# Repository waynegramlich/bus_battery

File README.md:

# bus_battery
A Bus module that senses battery voltage

## Revision A Issues

* R7 as 220 Ohm 3 resist SIP6 probably should be changed.

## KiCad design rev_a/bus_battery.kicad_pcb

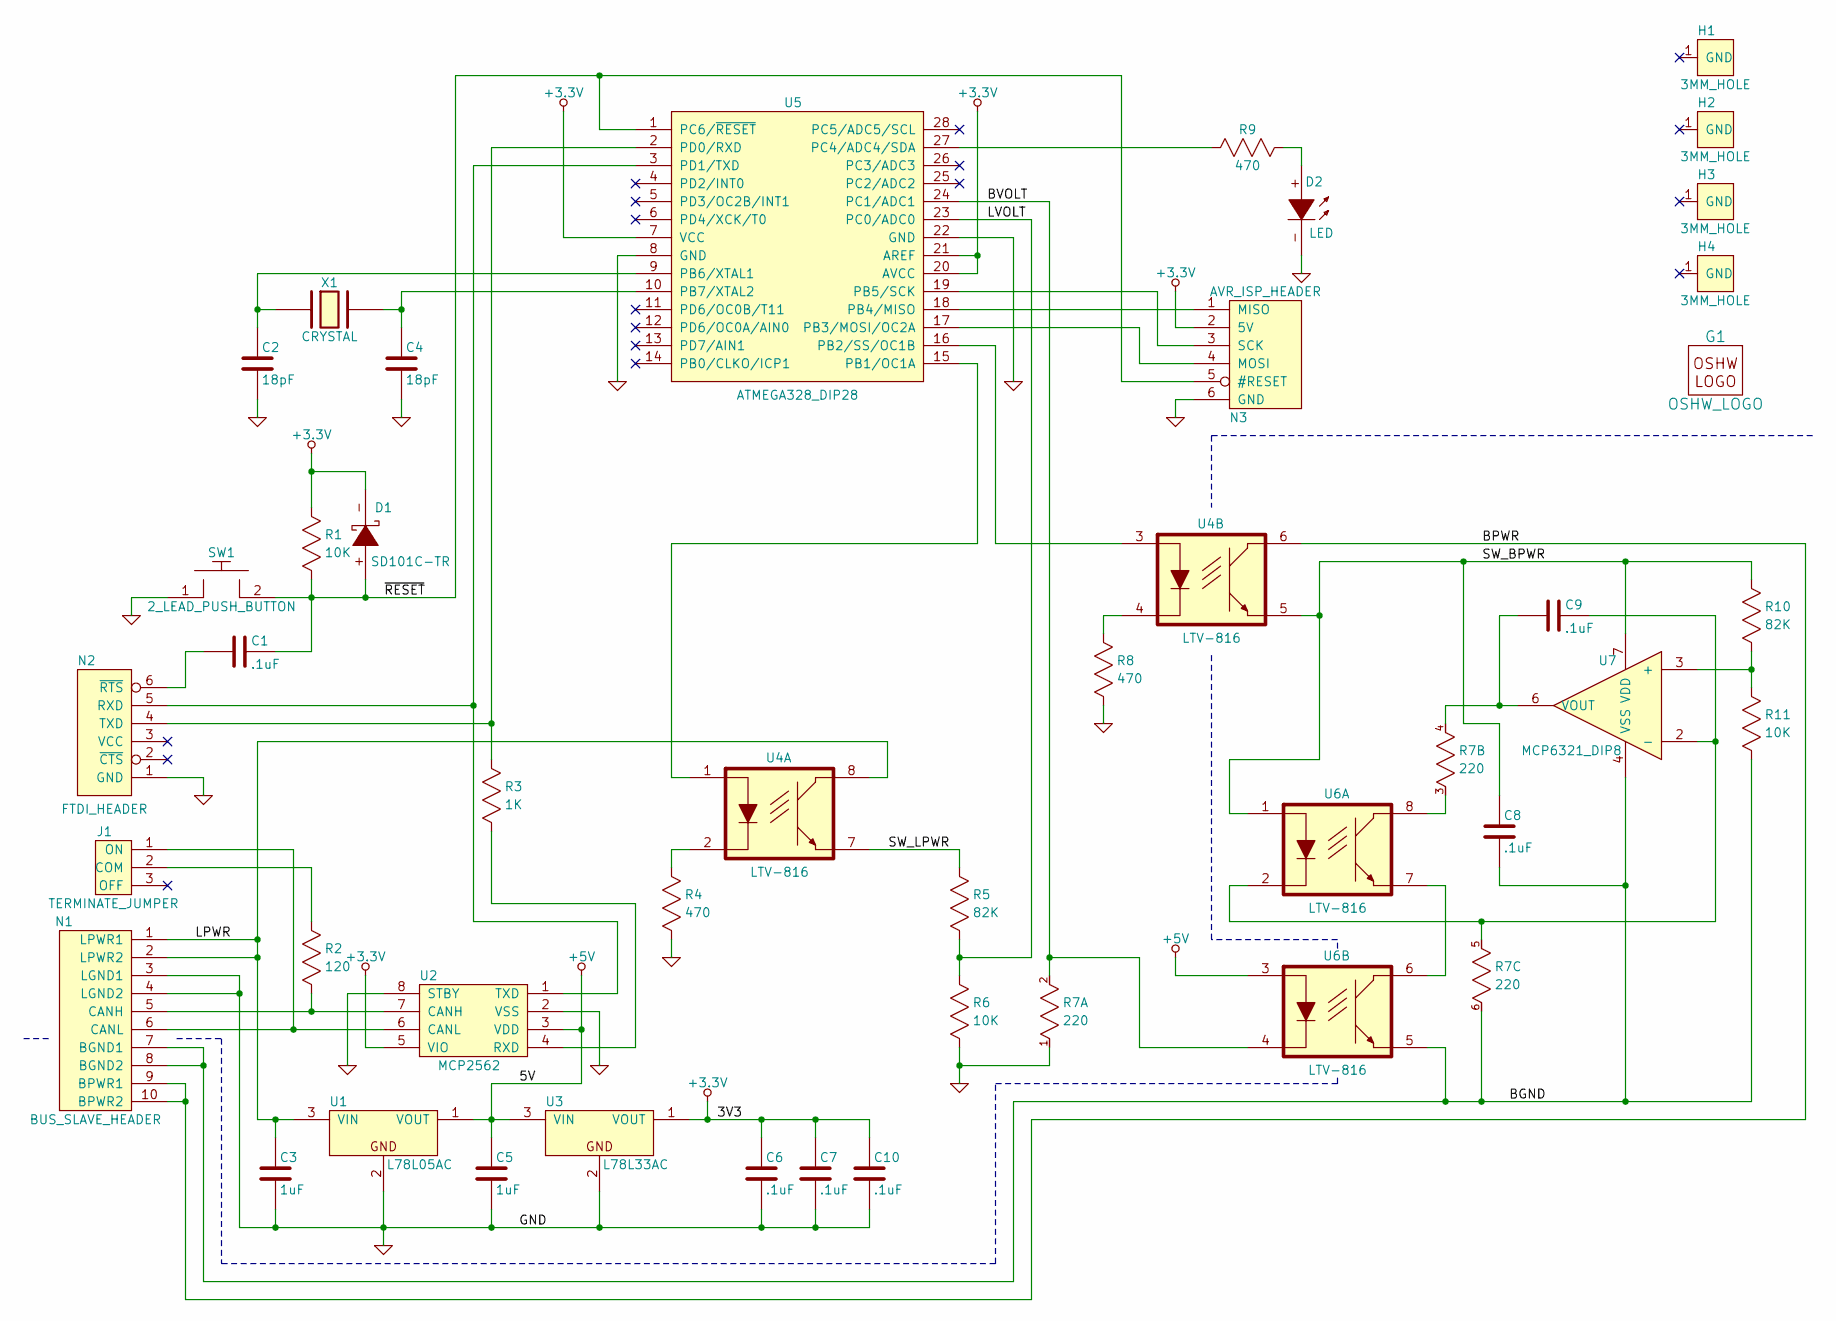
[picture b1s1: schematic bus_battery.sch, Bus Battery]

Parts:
C1, C6, C7, C8, C9, C10: .1uF; Capacitor3MMDiscRM2.5
C2, C4: 18pF; Capacitor3MMDiscRM2.5
C3, C5: 1uF; Capacitor3MMDiscRM2.5
D1: SD101C-TR; Diode_DO-41_SOD81_Horizontal_RM10
D2: LED; T1_LED
G1: OSHW_LOGO; OSHW_LOGO_150mil
H1, H2, H3, H4: 3MM_HOLE; MountingHole_3mm
J1: TERMINATE_JUMPER; Pin_Header_Straight_1x03
N1: BUS_SLAVE_HEADER; Pin_Header_Straight_2x05_Shrouded
N2: FTDI_HEADER; Pin_Header_Straight_1x06
N3: AVR_ISP_HEADER; Pin_Header_Straight_2x03
R1, R6, R11: 10K; R_HORIZ_300
R2: 120; R_HORIZ_300
R3: 1K; R_HORIZ_300
R4, R8, R9: 470; R_HORIZ_300
R5, R10: 82K; R_HORIZ_300
R7: 220; Pin_Header_Straight_1x06
SW1: 2_LEAD_PUSH_BUTTON; Button_6.5MM
U1: L78L05AC; TO92_123
U2: MCP2562; DIP-8__300
U3: L78L33AC; TO92_123
U4: LTV-816; DIP-8__300
U5: ATMEGA328_DIP28; DIP-28__300
U6: LTV-816
U7: MCP6321_DIP8; DIP-8__300
X1: CRYSTAL; Crystal_HC49-U_Vertical

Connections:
+3.3V: C6.1, C7.1, C10.1, D1.-, N3.2 (5V), R1.2, U2.5 (VIO), U3.1 (VOUT), U5.7 (VCC), U5.20 (AVCC), U5.21 (AREF)
+5V: C5.1, U1.1 (VOUT), U2.3 (VDD), U3.3 (VIN), U6.3
/BGND: C8.2, N1.7 (BGND1), N1.8 (BGND2), R7.6, R11.1, U6.5, U7.4 (VSS)
/BPWR: N1.9 (BPWR1), N1.10 (BPWR2), U4.6
/BVOLT: R7.2 (5), U5.24 (PC1/ADC1), U6.4
/LPWR: C3.1, N1.1 (LPWR1), N1.2 (LPWR2), U1.3 (VIN), U4.8
/LVOLT: R5.1, R6.2, U5.23 (PC0/ADC0)
/SW_BPWR: C8.1, R10.2, U4.5, U6.1, U7.7 (VDD)
/SW_LPWR: R5.2, U4.7
/~RESET: C1.2, D1.+, N3.5 (#RESET), R1.1, SW1.2, U5.1 (PC6/~RESET)
GND: C2.2, C3.2, C4.2, C5.2, C6.2, C7.2, C10.2, D2.-, N1.3 (LGND1), N1.4 (LGND2), N2.1 (GND), N3.6 (GND), R4.1, R6.1, R7.1 (6), R8.1, SW1.1, U1.2, U2.2 (VSS), U2.8 (STBY), U3.2, U5.8 (GND), U5.22 (GND)
unnamed: C1.1, N2.6 (~RTS)
unnamed: C2.1, U5.9 (PB6/XTAL1), X1.1
unnamed: C4.1, U5.10 (PB7/XTAL2), X1.2
unnamed: C9.1, R7.4 (5), U7.6 (VOUT)
unnamed: C9.2, R7.5, U6.2, U7.2 (-)
unnamed: D2.+, R9.2
unnamed: J1.1 (ON), N1.6 (CANL), U2.6 (CANL)
unnamed: J1.2 (COM), R2.2
unnamed: N1.5 (CANH), R2.1, U2.7 (CANH)
unnamed: N2.4 (TXD), R3.2, U5.2 (PD0/RXD)
unnamed: N2.5 (RXD), U2.1 (TXD), U5.3 (PD1/TXD)
unnamed: N3.1 (MISO), U5.18 (PB4/MISO)
unnamed: N3.3 (SCK), U5.19 (PB5/SCK)
unnamed: N3.4 (MOSI), U5.17 (PB3/MOSI/OC2A)
unnamed: R3.1, U2.4 (RXD)
unnamed: R4.2, U4.2
unnamed: R7.3 (6), U6.8
unnamed: R8.2, U4.4
unnamed: R9.1, U5.27 (PC4/ADC4/SDA)
unnamed: R10.1, R11.2, U7.3 (+)
unnamed: U4.1, U5.15 (PB1/OC1A)
unnamed: U4.3, U5.16 (PB2/SS/OC1B)
unnamed: U6.6, U6.7

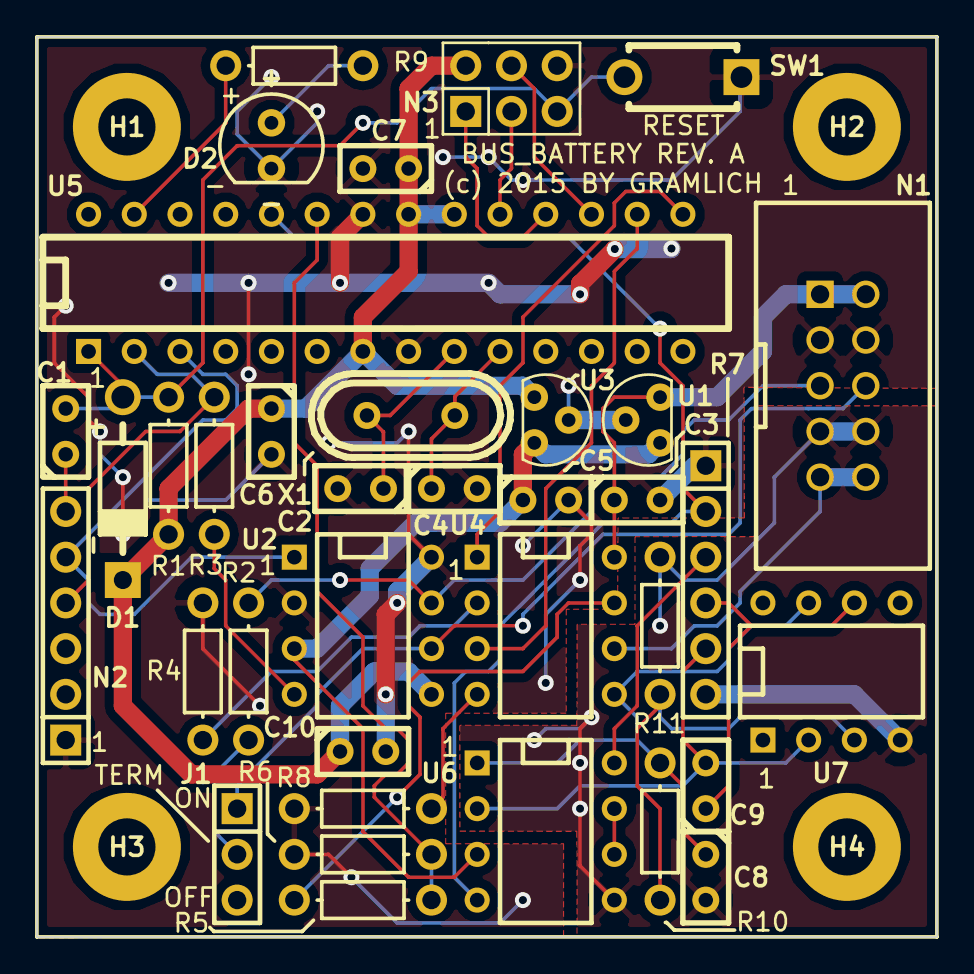
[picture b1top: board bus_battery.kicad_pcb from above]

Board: 2 copper layers, 50.0 x 50.0 mm, 41 parts (1 on the bottom side), 34 nets.

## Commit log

2015-01-13 Created an empty board.
2015-01-13 Concluded that this will have to be a 5cm x 10cm board.
2015-01-27 Finished off Rev. A.
2015-01-27 Noticed that mounting holes were not covered.
2015-02-13 Split 22uF capacitor into Aluminum and Tantulum.

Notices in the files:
rev_a/bus_battery.kicad_pcb:
COPYRIGHT (C) 2015  BY WAYNE GRAMLICH
(c) 2015 BY GRAMLICH
